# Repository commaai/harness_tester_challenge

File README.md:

<div align="center">
<h1>Harness Tester Challenge</h1>
<h3>
  <a href="https://comma.ai/leaderboard">Leaderboard</a>
  <span> · </span>
  <a href="https://comma.ai/jobs">comma.ai/jobs</a>
  <span> · </span>
  <a href="https://discord.comma.ai">Discord</a>
  <span> · </span>
  <a href="https://x.com/comma_ai">X</a>
</h3>
</div>

We (mock) designed a simple harness testing PCB and wrote some firmware for it. Unfortunately, this board was designed and firmware was written on a Monday morning.

<b>Can you figure out everything wrong with it?</b>

## The Harness Tester
We currently ship hundreds of [car-specific harnesses](https://www.comma.ai/shop/car-harness) to users every month, consisting of more than [40 different types](https://github.com/commaai/hardware/tree/master/harness/v3).

As a simple wiring harness, we expect them to have a near-zero failure rate, so good testing is critical.
This tester is designed to be capable of quickly verifying which pins are connected to which other pins.

A quick list of design goals is listed here:
- 12V DC input with transient and reverse polarity protection
- compatible with harnesses with up to 40 pins (through a pin header)
- start button and RGB LED are the user interface
- microSD card to store test results along with the current time (for statistical purposes)
- receive time by acquiring a GPS lock (*ok, yes, this is just to make the board and firmware more interesting*)

## The challenge
The challenge consists of 3 distinct parts, each riddled with more than a few bugs:
- Schematic ([PDF](./schematic.pdf) / [Web](https://kicanvas.org/?github=https%3A%2F%2Fgithub.com%2Fcommaai%2Fharness_tester_challenge%2Fblob%2Fmaster%2Fkicad_files%2Fhardware_challenge.kicad_sch))
- PCB layout ([Gerbers](./gerbers.zip) / [Web](https://kicanvas.org/?github=https%3A%2F%2Fgithub.com%2Fcommaai%2Fharness_tester_challenge%2Fblob%2Fmaster%2Fkicad_files%2Fhardware_challenge.kicad_pcb))
- Firmware ([Source](./firmware/))

The board is designed in [KiCad 8](https://www.kicad.org/), and the full project is available in an [exported archive](./kicad_project.zip).

There are a handful of intentional, show-stopping bugs hidden in each part. Find them, and [send](https://forms.gle/US88Hg7UR6bBuW3BA) them over to us for verification!

We're not looking for improvements or fixes; just submit a list of bugs.

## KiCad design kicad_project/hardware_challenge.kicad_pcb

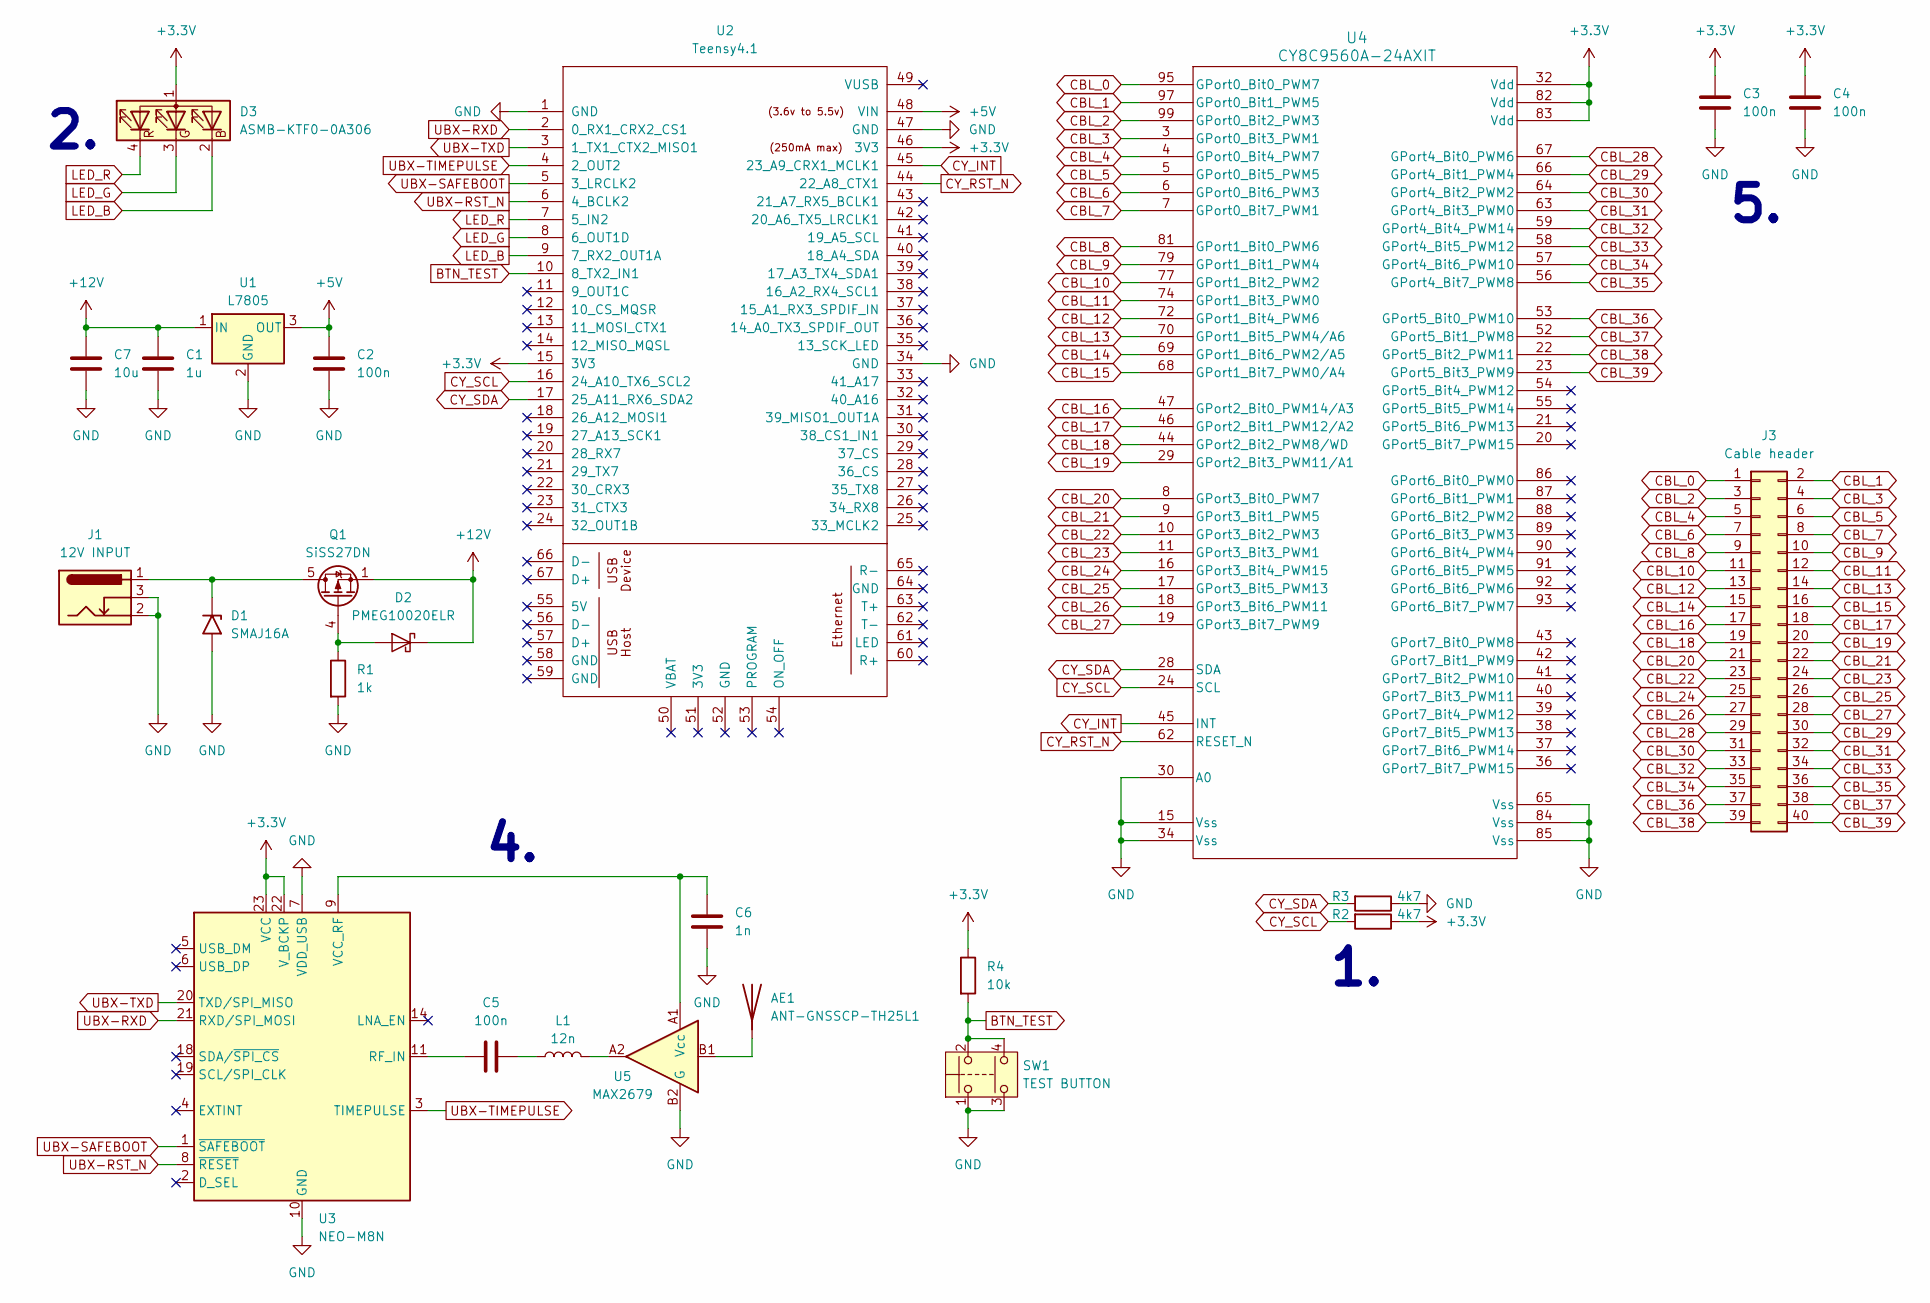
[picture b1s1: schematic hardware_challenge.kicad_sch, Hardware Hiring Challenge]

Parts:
AE1: ANT-GNSSCP-TH25L1
C1: 1u; C_0402_1005Metric
C2, C3, C4, C5: 100n; C_0402_1005Metric
C6: 1n; C_0402_1005Metric
C7: 10u; C_0402_1005Metric
D1: SMAJ16A; D_SMA
D2: PMEG10020ELR; Nexperia_CFP3_SOD-123W
D3: ASMB-KTF0-0A306; LED_ASMB-KTF0-0A306
J1: 12V INPUT; BarrelJack_CLIFF_FC681465S_SMT_Horizontal
J3: Cable header; PinHeader_2x20_P2.54mm_Horizontal
L1: 12n; L_0402_1005Metric
Q1: SiSS27DN; Vishay_PowerPAK_1212-8_Single
R1: 1k; R_0402_1005Metric
R2, R3: 4k7; R_0402_1005Metric
R4: 10k; R_0402_1005Metric
SW1: TEST BUTTON; SW_SPST_PTS645
U1: L7805; TO-252-2
U2: Teensy4.1; Teensy41
U3: NEO-M8N; ublox_NEO
U4: CY8C9560A-24AXIT; TQFP-100_12x12mm_P0.4mm
U5: MAX2679; WLP-4_0.83x0.83mm_P0.4mm

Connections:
+3.3V: C3.1, C4.1, D3.1 (A), R2.1, R4.1, U2.15 (3V3), U2.46 (3V3), U3.22 (V_BCKP), U3.23 (VCC), U4.32 (Vdd), U4.82 (Vdd), U4.83 (Vdd)
+5V: C2.1, U1.3 (OUT), U2.48 (VIN)
+12V: C1.1, C7.1, D2.1 (K), Q1.1 (S), Q1.2 (S), Q1.3 (S), U1.1 (IN)
BTN_TEST: R4.2, SW1.2, SW1.4, U2.10 (8_TX2_IN1)
CBL_0: J3.1, U4.95 (GPort0_Bit0_PWM7)
CBL_1: J3.2, U4.97 (GPort0_Bit1_PWM5)
CBL_2: J3.3, U4.99 (GPort0_Bit2_PWM3)
CBL_3: J3.4, U4.3 (GPort0_Bit3_PWM1)
CBL_4: J3.5, U4.4 (GPort0_Bit4_PWM7)
CBL_5: J3.6, U4.5 (GPort0_Bit5_PWM5)
CBL_6: J3.7, U4.6 (GPort0_Bit6_PWM3)
CBL_7: J3.8, U4.7 (GPort0_Bit7_PWM1)
CBL_8: J3.9, U4.81 (GPort1_Bit0_PWM6)
CBL_9: J3.10, U4.79 (GPort1_Bit1_PWM4)
CBL_10: J3.11, U4.77 (GPort1_Bit2_PWM2)
CBL_11: J3.12, U4.74 (GPort1_Bit3_PWM0)
CBL_12: J3.13, U4.72 (GPort1_Bit4_PWM6)
CBL_13: J3.14, U4.70 (GPort1_Bit5_PWM4/A6)
CBL_14: J3.15, U4.69 (GPort1_Bit6_PWM2/A5)
CBL_15: J3.16, U4.68 (GPort1_Bit7_PWM0/A4)
CBL_16: J3.17, U4.47 (GPort2_Bit0_PWM14/A3)
CBL_17: J3.18, U4.46 (GPort2_Bit1_PWM12/A2)
CBL_18: J3.19, U4.44 (GPort2_Bit2_PWM8/WD)
CBL_19: J3.20, U4.29 (GPort2_Bit3_PWM11/A1)
CBL_20: J3.21, U4.8 (GPort3_Bit0_PWM7)
CBL_21: J3.22, U4.9 (GPort3_Bit1_PWM5)
CBL_22: J3.23, U4.10 (GPort3_Bit2_PWM3)
CBL_23: J3.24, U4.11 (GPort3_Bit3_PWM1)
CBL_24: J3.25, U4.16 (GPort3_Bit4_PWM15)
CBL_25: J3.26, U4.17 (GPort3_Bit5_PWM13)
CBL_26: J3.27, U4.18 (GPort3_Bit6_PWM11)
CBL_27: J3.28, U4.19 (GPort3_Bit7_PWM9)
CBL_28: J3.29, U4.67 (GPort4_Bit0_PWM6)
CBL_29: J3.30, U4.66 (GPort4_Bit1_PWM4)
CBL_30: J3.31, U4.64 (GPort4_Bit2_PWM2)
CBL_31: J3.32, U4.63 (GPort4_Bit3_PWM0)
CBL_32: J3.33, U4.59 (GPort4_Bit4_PWM14)
CBL_33: J3.34, U4.58 (GPort4_Bit5_PWM12)
CBL_34: J3.35, U4.57 (GPort4_Bit6_PWM10)
CBL_35: J3.36, U4.56 (GPort4_Bit7_PWM8)
CBL_36: J3.37, U4.53 (GPort5_Bit0_PWM10)
CBL_37: J3.38, U4.52 (GPort5_Bit1_PWM8)
CBL_38: J3.39, U4.22 (GPort5_Bit2_PWM11)
CBL_39: J3.40, U4.23 (GPort5_Bit3_PWM9)
CY_INT: U2.45 (23_A9_CRX1_MCLK1), U4.45 (INT)
CY_RST_N: U2.44 (22_A8_CTX1), U4.62 (RESET_N)
CY_SCL: R2.2, U2.16 (24_A10_TX6_SCL2), U4.24 (SCL)
CY_SDA: R3.2, U2.17 (25_A11_RX6_SDA2), U4.28 (SDA)
GND: C1.2, C2.2, C3.2, C4.2, C6.2, C7.2, D1.2 (A2), J1.2, J1.3, R1.2, R3.1, SW1.1, SW1.3, U1.2 (GND), U2.1 (GND), U2.34 (GND), U2.47 (GND), U3.7 (VDD_USB), U3.10 (GND), U3.12 (GND), U3.13 (GND), U3.24 (GND), U4.15 (Vss), U4.30 (A0), U4.34 (Vss), U4.65 (Vss), U4.84 (Vss), U4.85 (Vss), U5.B2 (G)
LED_B: D3.2 (BK), U2.9 (7_RX2_OUT1A)
LED_G: D3.3 (GK), U2.8 (6_OUT1D)
LED_R: D3.4 (RK), U2.7 (5_IN2)
unnamed: AE1.1 (A), U5.B1
unnamed: C5.2, L1.1
unnamed: D1.1 (A1), J1.1, Q1.5 (D)
unnamed: D2.2 (A), Q1.4 (G), R1.1
unnamed: L1.2, U5.A2
unnamed: C5.1, U3.11 (RF_IN)
unnamed: C6.1, U3.9 (VCC_RF), U5.A1 (Vcc)
UBX-RST_N: U2.6 (4_BCLK2), U3.8 (~RESET)
UBX-RXD: U2.2 (0_RX1_CRX2_CS1), U3.21 (RXD/SPI_MOSI)
UBX-SAFEBOOT: U2.5 (3_LRCLK2), U3.1 (~SAFEBOOT)
UBX-TIMEPULSE: U2.4 (2_OUT2), U3.3 (TIMEPULSE)
UBX-TXD: U2.3 (1_TX1_CTX2_MISO1), U3.20 (TXD/SPI_MISO)

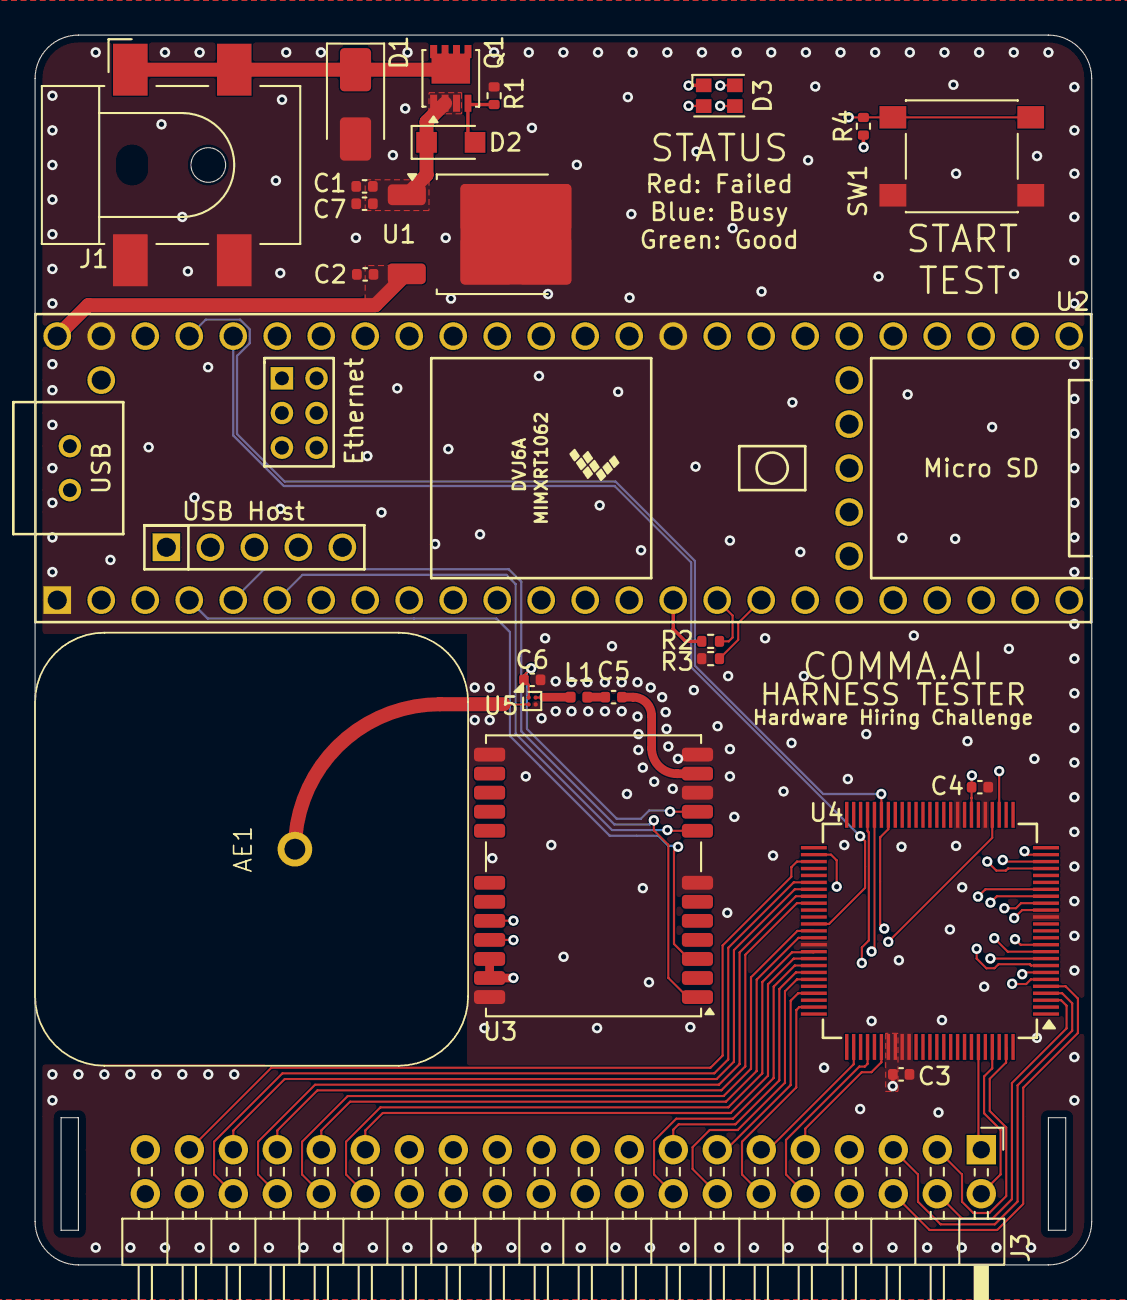
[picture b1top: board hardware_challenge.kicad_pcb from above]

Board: 4 copper layers, 61.0 x 71.0 mm, 25 parts (0 on the bottom side), 64 nets.

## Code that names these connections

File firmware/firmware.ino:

#include <SD.h>
#include <ctype.h>
#include "CY8C9560.h"

enum Status {FAILED, BUSY, GOOD};

#define PIN_UBX_TIMEPULSE 2
#define PIN_UBX_SAFEBOOT 3
#define PIN_UBX_RST_N 4
#define PIN_LED_R 5
#define PIN_LED_G 6
#define PIN_LED_B 7
#define PIN_BTN_TEST 8

#define DBG_SERIAL Serial
#define UBX_SERIAL Serial1
#define SD_CS BUILTIN_SDCARD

#define NUM_HARNESS_PINS 40
// Example connection matrix, just for illustration
const uint64_t EXPECTED_CONNECTIONS[NUM_HARNESS_PINS] = {
  0b1000000000000000000000000010000000000000,
  0b0100001000000000000000000000000000000000,
  0b0010000000000000000000000000000000000000,
  0b0001100000001000000000000000000010000000,
  0b0000100000100000000000000001000000000000,
  0b0000010100000000000000000000000000000000,
  0b0000001000000000100000000000000000000000,
  0b0000000100000000000000000000001000001000,
  0b0000000010000000000000000000000000000000,
  0b0000000001000000000000000000000010000000,
  0b0010000000100000000000000000000000000000,
  0b0000000000010000000010000000000000000000,
  0b0000000000001000000000000000000000010000,
  0b0000000000000100000000000000000000000001,
  0b0000000000000010000000001000000000000000,
  0b0000000000001001000000000100000000000000,
  0b0000000000000000100000000000000000000000,
  0b0000010000000000010000000000000000000000,
  0b0000000000000000001000000000000000000000,
  0b0000000000000000000100000000100000000000,
  0b0000000000000000000010000000000000000000,
  0b0000000000000000000001000000000000000000,
  0b0000000000000000000000100000000000000000,
  0b0000000000000000000000010000000001000000,
  0b0000000000000000000000001000000000000000,
  0b0000000000001000000000000100000000000000,
  0b0000000000000000000000000010000000000000,
  0b0000000000100010000000001001000000001000,
  0b0000000000000000000000000000100000000000,
  0b0000000000001000000000000000010000010000,
  0b0000000000000000000000000000001000000000,
  0b0000000000000000000000000000000100000000,
  0b0000000000000000000000000000000010100000,
  0b0000000000000000000000000000000001000010,
  0b0000100000000000000000100000000000100000,
  0b0000010000000000000000000000000000011000,
  0b0000000000000000000000000000000000001000,
  0b0000000000000000000000000000010000000100,
  0b0000000000000000000000000000000000000010,
  0b0000000000000000000000000000000000000001,
};

CY8C9560 cy;
char utc_time[20], date[20];
bool time_fixed = false;

void set_status(Status s) {
  digitalWrite(PIN_LED_R, !(s == FAILED));
  digitalWrite(PIN_LED_B, !(s == BUSY));
  digitalWrite(PIN_LED_G, !(s == GOOD));
}

bool valid_nmea_checksum(const char *sentence) {
    if (sentence[0] != '$') return false;
    // find the checksum starting point
    const char *asterisk = strchr(sentence, '*');
    if (asterisk == nullptr || strlen(asterisk) < 3) return false;
    // verify checksum is valid hex
    if (!isxdigit(asterisk[1]) || !isxdigit(asterisk[2])) return false;
    uint8_t checksum = 0;
    for (const char *p = sentence + 1; p < asterisk; p++) {
        checksum ^= static_cast<uint8_t>(*p);
    }
    // get the checksum from the sentence
    char received_str[3] = {asterisk[1], asterisk[2], '\0'};
    uint8_t received = static_cast<uint8_t>(strtoul(received_str, nullptr, 16));
    return checksum == received;
}

void process_nmea(char *buf, int len) {
  buf[len] = 0;
  if (strncmp(buf, "$GPRMC", 6) != 0) return;
  if (!valid_nmea_checksum(buf)) {
    DBG_SERIAL.println("Bad NMEA checksum");
    return;
  }

  char status;
  char new_utc_time[20];
  char new_date[20];
  int fields = sscanf(buf, "$GPRMC,%10[^,],%c,%*f,%*c,%*f,%*c,%*f,%*f,%6[^,]", new_utc_time, &status, new_date);

  if (fields != 3) {
    DBG_SERIAL.println("Failed to parse $GPRMC");
    return;
  }
  if (status != 'A') {
    time_fixed = false;
    return;
  }
  strcpy(utc_time, new_utc_time);
  strcpy(date, new_date);
  if (!time_fixed) {
    DBG_SERIAL.println("Time received. Ready to test some harnesses!");
    set_status(GOOD);
    time_fixed = true;
  }
}

void log_result(bool passed) {
  File f = SD.open("results.txt", FILE_WRITE);
  if (f) {
    f.print(date); f.print(" - "); f.print(utc_time); f.print(": "); // raw date + time strings are fine here
    f.println(passed ? "Passed" : "Failed");
    f.close();
  } else {
    DBG_SERIAL.println("Failed to open log file");
  }
}

void setup() {
  // Serial ports
  DBG_SERIAL.begin(115200);
  UBX_SERIAL.begin(9600);

  // Initialize RGB LED GPIO
  pinMode(PIN_LED_R, OUTPUT);
  pinMode(PIN_LED_G, OUTPUT);
  pinMode(PIN_LED_B, OUTPUT);

  // GPIO
  set_status(BUSY);
  pinMode(PIN_BTN_TEST, INPUT);
  pinMode(PIN_UBX_TIMEPULSE, INPUT);
  pinMode(PIN_UBX_SAFEBOOT, OUTPUT);
  pinMode(PIN_UBX_RST_N, OUTPUT);
  digitalWrite(PIN_UBX_SAFEBOOT, LOW);
  digitalWrite(PIN_UBX_RST_N, HIGH);

  // CY8C9560
  if(!cy.begin()) {
    DBG_SERIAL.println("CY8C9560 initialization failed");
    while (1);
  }

  // SD card
  if (!SD.begin(SD_CS)) {
    DBG_SERIAL.println("SD card initialization failed");
    while (1);
  }

  DBG_SERIAL.println("Waiting for GPS time lock...");
}
bool last_passed = true;
char nmea_buf[128];
int nmea_idx = 0;
void loop() {
  static bool discarding_nmea = false;
  // Process incoming ublox messages
  while (UBX_SERIAL.available()) {
    char next_byte = UBX_SERIAL.read();

    // discard sequence until current sentence finishes
    if (discarding_nmea) {
        if (next_byte == '\n') {
            discarding_nmea = false;
            nmea_idx = 0;
        }
        continue;
    }

    if (next_byte == '\r') continue;

    if (next_byte == '\n') {
      process_nmea(nmea_buf, nmea_idx);
      nmea_idx = 0;

      // Jump out the while here to make sure we're not missing any button presses under high load
      break;
    }

    if (nmea_idx < sizeof(nmea_buf) - 1) {
      nmea_buf[nmea_idx++] = next_byte;
    } else {
      // discard/reset oversized sentence
      nmea_idx = 0;
      discarding_nmea = true;
    }
  }

  // Return if we don't have a time fix yet
  if (!time_fixed) return;
  set_status(last_passed ? GOOD : FAILED);

  // Button edge trigger
  static bool previous_button = HIGH;
  bool current_button = digitalRead(PIN_BTN_TEST);
  bool button_pressed = previous_button == HIGH && current_button == LOW;
  previous_button = current_button;

  // Start testing only if the button is pressed
  if (!button_pressed) return;  // active low
  set_status(BUSY);

  // Test harness by checking the connectivity of every pin
  bool passed = true;
  for (int i = 0; i < NUM_HARNESS_PINS; i++) {
    uint64_t output_mask = 1ULL << i; // Should be shifted by an unsigned long long
    if (!cy.set_output(output_mask, output_mask)) {
      DBG_SERIAL.println("Failed to configure output");
      passed = false;
      break;
    }
    if (!cy.set_pd_inputs(~output_mask)) {
      DBG_SERIAL.println("Failed to configure inputs");
      passed = false;
      break;
    }
    uint64_t values;
    if (!cy.read_inputs(values)) {
      DBG_SERIAL.println("Failed to read inputs");
      passed = false;
      break;
    }
    values &= ~output_mask;

    // Log connections to the serial port
    DBG_SERIAL.printf("Pin %d: ", i);
    for (int j = 0; j < NUM_HARNESS_PINS; j++) DBG_SERIAL.printf("%d", (values & (1ULL << j)) ? 1 : 0); // Should be shifted by an unsigned long long
    DBG_SERIAL.println();

    if (values != EXPECTED_CONNECTIONS[i]) {
      passed = false;
    }
  }

  // Show and log results
  DBG_SERIAL.println(passed ? "Harness passed!" : "Harness failed!");
  last_passed = passed;
  log_result(passed);
  set_status(passed ? GOOD : FAILED);
}

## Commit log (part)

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2024-05-31 hardware challenge
2024-08-12 add header with leaderboard
2024-08-12 form link
2026-06-04 add harness tester bug list
2026-06-06 Document harness tester challenge bugs
2026-06-06 Refine harness tester bug list
